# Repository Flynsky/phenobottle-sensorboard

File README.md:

# Phenobottle Sensorboard

## Getting Startet
- Connect via USB or USART0 to access a internal console.
  A good, easy to use Tool for this is the Arduino IDE. 
- Send "?" to this console for help on the avaliable commands.

## Picture

## Hardware

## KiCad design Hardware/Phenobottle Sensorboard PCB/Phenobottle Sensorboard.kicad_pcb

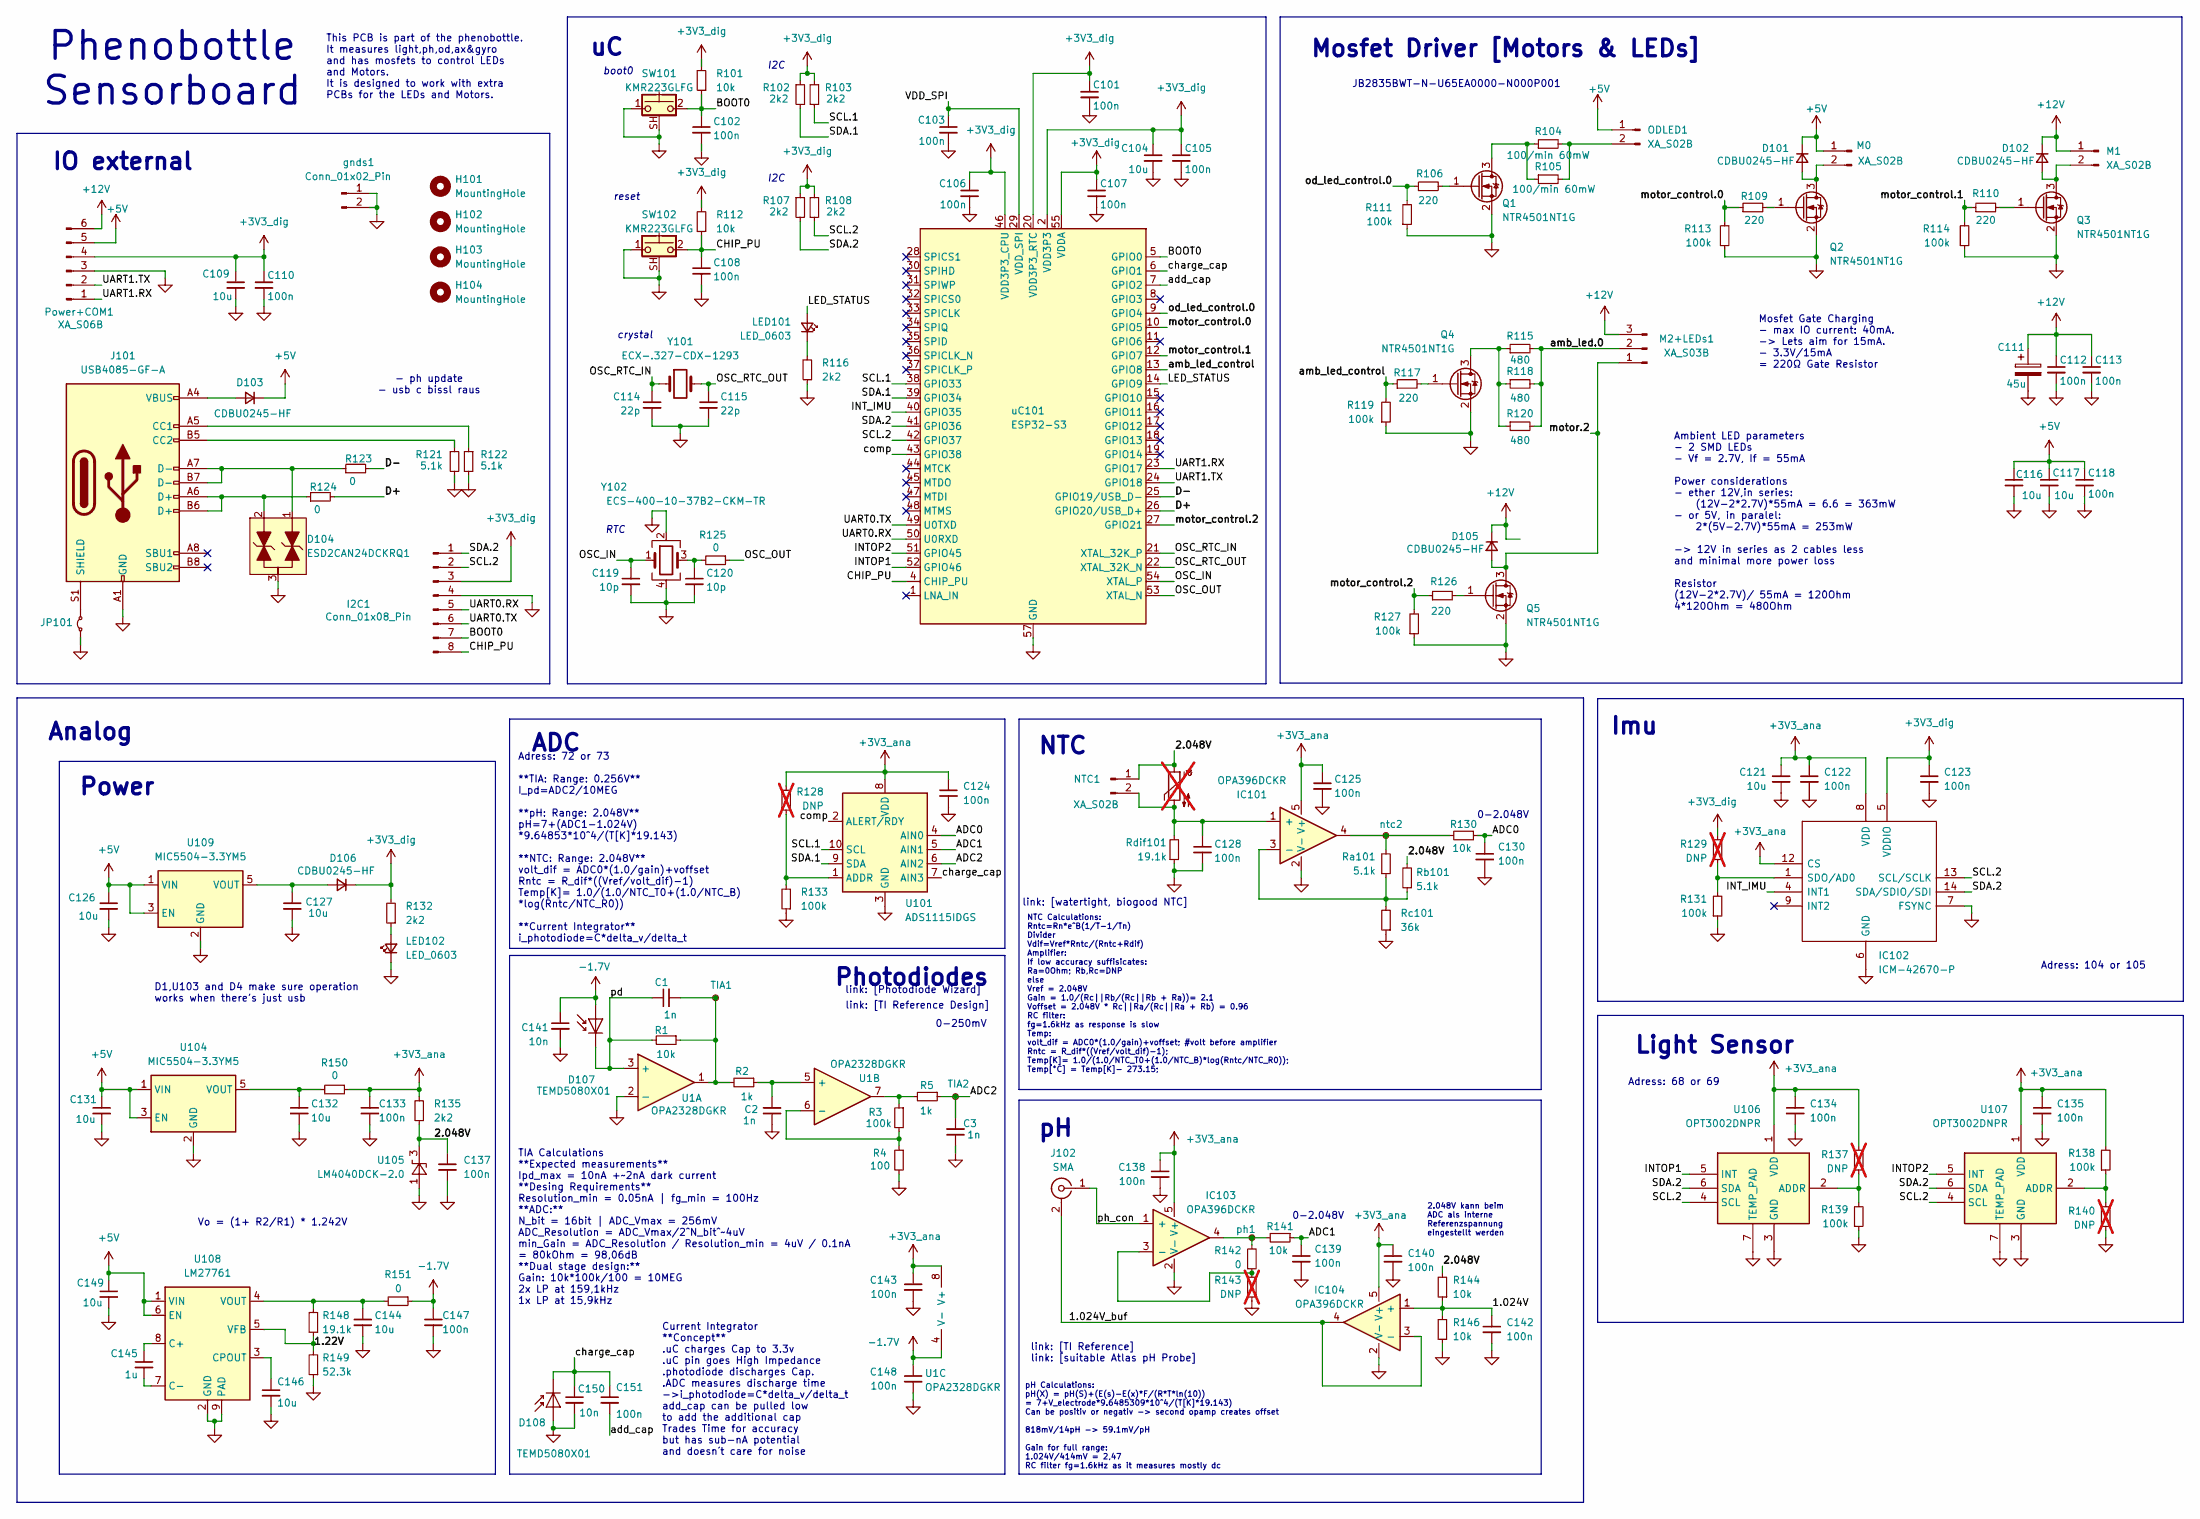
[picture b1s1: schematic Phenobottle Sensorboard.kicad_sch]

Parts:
C1, C2, C3: 1n; C_0603_1608Metric_Pad1.08x0.95mm_HandSolder
C101, C102, C103, C105, C106, C107, C108, C110, C118, C122, C123, C124, C125, C128, C130, C133, C134, C135, C137, C138, C139, C140, C142, C143, C147, C148: 100n; C_0402_1005Metric_Pad0.74x0.62mm_HandSolder
C104, C109, C116, C117, C121, C126, C127, C131, C132, C144, C146, C149: 10u; C_0805_2012Metric_Pad1.18x1.45mm_HandSolder
C111: 45u; CP_Elec_6.3x7.7
C112, C113, C151: 100n; C_0603_1608Metric
C114, C115: 22p; C_0603_1608Metric
C119, C120: 10p; C_0603_1608Metric
C141, C150: 10n; C_0603_1608Metric
C145: 1u; C_0805_2012Metric_Pad1.18x1.45mm_HandSolder
D101, D102, D103, D105, D106: CDBU0245-HF; DIOM179X85N; Mouser Part Number 78-V1FM15-M3/I; mouser 78-V1FM15-M3/I
D104: ESD2CAN24DCKRQ1; SOT-323_SC-70; Manufacturer_Part_Number ESD2CAN24DCKRQ1; Mouser Part Number 595-ESD2CAN24DCKRQ1
D107, D108: TEMD5080X01; Mouser Part Number 720-SFH2440
H101, H102, H103, H104: MountingHole; MountingHole_3.2mm_M3_Pad_Via
I2C1: Conn_01x08_Pin; PinHeader_1x08_P2.54mm_Vertical
IC101, IC103, IC104: OPA396DCKR; SOT65P210X110-5N; Mouser Part Number 595-OPA396DCKR
IC102: ICM-42670-P; ICM42670P; Mouser Part Number 410-ICM-42670-P
J101: USB4085-GF-A; USB_C_Receptacle_GCT_USB4085; Mouser Part Number 640-USB4085-GF-A
J102: SMA; SMA_Wurth_60312002114503_Vertical; Mouser Part Number 737-RF203ET0050G; mouser 471-SMARACONNECTOR
JP101: 0; R_0603_1608Metric_Pad0.98x0.95mm_HandSolder
LED101, LED102: LED_0603; LED_0603_1608Metric_Pad1.05x0.95mm_HandSolder
M0, M1: XA_S02B; JST_XA_S02B-XASK-1_1x02_P2.50mm_Horizontal
M2+LEDs1: XA_S03B; JST_XA_S03B-XASK-1_1x03_P2.50mm_Horizontal
NTC1: XA_S02B; JST_XA_S02B-XASK-1_1x02_P2.50mm_Horizontal
ODLED1: XA_S02B; JST_XA_S02B-XASK-1_1x02_P2.50mm_Horizontal
Power+COM1: XA_S06B; JST_XA_S06B-XASK-1_1x06_P2.50mm_Horizontal
Q1, Q2, Q3, Q4, Q5: NTR4501NT1G; SOT-23-3; Mouser Part Number 863-NTR4501NT1G
R1, R101, R112, R130, R141, R144, R146: 10k; R_0603_1608Metric_Pad0.98x0.95mm_HandSolder
R2, R5: 1k; R_0603_1608Metric_Pad0.98x0.95mm_HandSolder
R3, R111, R113, R114, R119, R127, R131, R133, R138, R139: 100k; R_0603_1608Metric_Pad0.98x0.95mm_HandSolder
R4: 100; R_0603_1608Metric_Pad0.98x0.95mm_HandSolder
R102, R103, R107, R108, R116, R132, R135: 2k2; R_0603_1608Metric_Pad0.98x0.95mm_HandSolder
R104, R105: 100/min 60mW; R_0603_1608Metric_Pad0.98x0.95mm_HandSolder
R106, R109, R110, R117, R126: 220; R_0603_1608Metric_Pad0.98x0.95mm_HandSolder
R115, R118, R120: 480; R_0603_1608Metric_Pad0.98x0.95mm_HandSolder
R121, R122: 5.1k; R_0603_1608Metric_Pad0.98x0.95mm_HandSolder
R123, R124, R125, R142, R150, R151: 0; R_0603_1608Metric_Pad0.98x0.95mm_HandSolder
R128, R129, R137, R140, R143: DNP; R_0603_1608Metric_Pad0.98x0.95mm_HandSolder; not fitted
R148: 19.1k; R_0603_1608Metric_Pad0.98x0.95mm_HandSolder
R149: 52.3k; R_0603_1608Metric_Pad0.98x0.95mm_HandSolder
Ra101: 5.1k; R_0603_1608Metric_Pad0.98x0.95mm_HandSolder
Rb101: 5.1k; R_0603_1608Metric_Pad0.98x0.95mm_HandSolder
Rc101: 36k; R_0603_1608Metric_Pad0.98x0.95mm_HandSolder
Rdif101: 19.1k; R_0603_1608Metric_Pad0.98x0.95mm_HandSolder
SW101, SW102: KMR223GLFG; SW_SPST_CK_KMS2xxGP; Mouser Part Number 611-KMR223GLFG
TH101: Thermistor_NTC; mouser 527-JI-103C1R2-L301; not fitted
TIA1, TIA2: TestPoint_Small; TestPoint_Loop_D2.50mm_Drill1.0mm
U1: OPA2328DGKR; VSSOP-8_SOP65P490X110-8N; Mouser Part Number 595-OPT3002DNPR; mouser 595-OPA2328DGKR
U101: ADS1115IDGS; TSSOP-10_3x3mm_P0.5mm; Mouser Part Number 595-ADS1115IDGSR
U104, U109: MIC5504-3.3YM5; SOT-23-5
U105: LM4040DCK-2.0; SOT-353_SC-70-5; Mouser Part Number 595-M4040EIM7-2.0NPB
U106, U107: OPT3002DNPR; Mouser Part Number 595-OPT3002DNPR
U108: LM27761; WSON-8-1EP_2x2mm_P0.5mm_EP0.9x1.6mm; Mouser Part Number 595-LM27761DSGR
Y101: ECX-.327-CDX-1293; Crystal_SMD_3215-2Pin_3.2x1.5mm; Mouser Part Number 520-ECX-.327CDX-1293
Y102: ECS-400-10-37B2-CKM-TR; Crystal_SMD_2016-4Pin_2.0x1.6mm; Mouser Part Number 520-400-10-37B2CKMTR
gnds1: Conn_01x02_Pin; PinHeader_1x02_P2.54mm_Vertical
ntc2: TestPoint_Small; TestPoint_Loop_D2.50mm_Drill1.0mm
ph1: TestPoint_Small; TestPoint_Loop_D2.50mm_Drill1.0mm
uC101: ESP32-S3; QFN-56-1EP_7x7mm_P0.4mm_EP4x4mm; Mouser Part Number 356-ESP32-S3FH4R2

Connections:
+3V3_ana: C121.1, C122.1, C124.1, C125.1, C133.1, C134.1, C135.1, C138.1, C140.1, C143.1, IC101.5 (V+), IC102.8 (VDD), IC102.12 (CS), IC103.5 (V+), IC104.5 (V+), R128.2, R135.2, R137.1, R138.2, R150.1, U1.8 (V+), U101.8 (VDD), U106.1 (VDD), U107.1 (VDD)
+3V3_dig: C101.1, C104.1, C105.1, C106.1, C107.1, C109.1, C110.1, C123.1, D106.1 (K), I2C1.3, IC102.5 (VDDIO), Power+COM1.4, R101.2, R102.1, R103.1, R107.1, R108.1, R112.2, R129.1, R132.2, uC101.2 (VDD3P3), uC101.3 (VDD3P3), uC101.20 (VDD3P3_RTC), uC101.46 (VDD3P3_CPU), uC101.55 (VDDA), uC101.56 (VDDA)
+5V: C116.1, C117.1, C118.1, C126.1, C131.1, C149.1, D101.1 (K), D103.1 (K), M0.1, ODLED1.1, Power+COM1.5, U104.1 (VIN), U104.3 (EN), U108.1 (VIN), U108.6 (EN), U109.1 (VIN), U109.3 (EN)
+12V: C111.1, C112.1, C113.1, D102.1 (K), D105.1 (K), M1.1, M2+LEDs1.3, Power+COM1.6
-1.7V: C141.1, C147.1, C148.1, D107.2 (A), R151.1, U1.4 (V-)
/1.22V: R148.1, R149.2, U108.5 (VFB)
/1.024V: C142.1, IC104.1 (+), R144.1, R146.2
/1.024V_buf: IC104.3 (-), IC104.4, J102.2 (Ext)
/2.048V: C137.1, NTC1.1, R135.1, R144.2, Rb101.2, TH101.1, U105.3 (K)
/ADC0: C130.1, R130.1, U101.4 (AIN0)
/ADC1: C139.1, R141.1, U101.5 (AIN1)
/ADC2: C3.2, R5.1, TIA2.1, U101.6 (AIN2)
/BOOT0: C102.1, I2C1.7, R101.1, SW101.2, uC101.5 (GPIO0)
/CHIP_PU: C108.1, I2C1.8, R112.1, SW102.2, uC101.4 (CHIP_PU)
/D+: R124.2, uC101.26 (GPIO20/USB_D+)
/D-: R123.2, uC101.25 (GPIO19/USB_D-)
/INTOP1: U106.5 (INT), uC101.52 (GPIO46)
/INTOP2: U107.5 (INT), uC101.51 (GPIO45)
/INT_IMU: IC102.4 (INT1), uC101.40 (GPIO35)
/LED_STATUS: LED101.2 (A), uC101.14 (GPIO9)
/OSC_IN: C119.1, Y102.1, uC101.54 (XTAL_P)
/OSC_OUT: R125.1, uC101.53 (XTAL_N)
/OSC_RTC_IN: C114.1, Y101.1, uC101.21 (XTAL_32K_P)
/OSC_RTC_OUT: C115.1, Y101.2, uC101.22 (XTAL_32K_N)
/SCL.1: R103.2, U101.10 (SCL), uC101.38 (GPIO33)
/SCL.2: I2C1.2, IC102.13 (SCL/SCLK), R108.2, U106.4 (SCL), U107.4 (SCL), uC101.42 (GPIO37)
/SDA.1: R102.2, U101.9 (SDA), uC101.39 (GPIO34)
/SDA.2: I2C1.1, IC102.14 (SDA/SDIO/SDI), R107.2, U106.6 (SDA), U107.6 (SDA), uC101.41 (GPIO36)
/UART0.RX: I2C1.5, uC101.50 (U0RXD)
/UART0.TX: I2C1.6, uC101.49 (U0TXD)
/UART1.RX: Power+COM1.1, uC101.23 (GPIO17)
/UART1.TX: Power+COM1.2, uC101.24 (GPIO18)
/VDD_SPI: C103.1, uC101.29 (VDD_SPI)
/add_cap: C151.2, uC101.7 (GPIO2)
/amb_led.0: M2+LEDs1.2, R115.2, R118.2, R120.2
/amb_led_control: R117.1, R119.2, uC101.13 (GPIO8)
/charge_cap: C150.1, C151.1, D108.1 (K), U101.7 (AIN3), uC101.6 (GPIO1)
/comp: U101.2 (ALERT/RDY), uC101.43 (GPIO38)
/motor.2: D105.2 (A), M2+LEDs1.1, Q5.3 (D)
/motor_control.0: R109.1, R113.2, uC101.10 (GPIO5)
/motor_control.1: R110.1, R114.2, uC101.12 (GPIO7)
/motor_control.2: R126.1, R127.2, uC101.27 (GPIO21)
/od_led_control.0: R106.1, R111.2, uC101.9 (GPIO4)
/pd: C1.1, D107.1 (K), R1.2, U1.3 (+)
/ph_con: IC103.1 (+), J102.1 (In)
GND: C2.1, C3.1, C101.2, C102.2, C103.2, C104.2, C105.2, C106.2, C107.2, C108.2, C109.2, C110.2, C111.2, C112.2, C113.2, C114.2, C115.2, C116.2, C117.2, C118.2, C119.2, C120.2, C121.2, C122.2, C123.2, C124.2, C125.2, C126.2, C127.2, C128.2, C130.2, C131.2, C132.2, C133.2, C134.2, C135.2, C137.2, C138.2, C139.2, C140.2, C141.2, C142.2, C143.2, C144.2, C146.2, C147.2, C148.2, C149.2, C150.2, D104.3, D108.2 (A), I2C1.4, IC101.2 (V-), IC102.6 (GND), IC102.7 (FSYNC), IC103.2 (V-), IC104.2 (V-), J101.A1 (GND), J101.A12 (GND), J101.B1 (GND), J101.B12 (GND), JP101.1 (A), LED102.1 (K), Power+COM1.3, Q1.2 (S), Q2.2 (S), Q3.2 (S), Q4.2 (S), Q5.2 (S), R4.2, R111.1, R113.1, R114.1, R116.1, R119.1, R121.2, R122.2, R127.1, R131.1, R133.1, R139.1, R140.2, R143.1, R146.1, R149.1, Rc101.1, Rdif101.1, SW101.1, SW101.SH (B), SW102.1, SW102.SH (B), U1.2 (-), U101.3 (GND), U104.2 (GND), U105.1 (A), U106.3 (GND), U106.7 (TEMP_PAD), U107.3 (GND), U107.7 (TEMP_PAD), U108.2 (GND), U108.9 (PAD), U109.2 (GND), Y102.2, Y102.4, gnds1.1, gnds1.2, uC101.57 (GND)
unnamed: C1.2, R1.1, R2.2, TIA1.1, U1.1
unnamed: C120.1, R125.2, Y102.3
unnamed: D101.2 (A), M0.2, Q2.3 (D)
unnamed: D102.2 (A), M1.2, Q3.3 (D)
unnamed: D103.2 (A), J101.A4 (VBUS), J101.A9 (VBUS), J101.B4 (VBUS), J101.B9 (VBUS)
unnamed: D104.1, J101.A7 (D-), J101.B7 (D-), R123.1
unnamed: D104.2, J101.A6 (D+), J101.B6 (D+), R124.1
unnamed: C127.1, D106.2 (A), U109.5 (VOUT)
unnamed: C128.1, IC101.1 (+), NTC1.2, Rdif101.2, TH101.2
unnamed: IC101.3 (-), Ra101.1, Rb101.1, Rc101.2
unnamed: IC101.4, R130.2, Ra101.2, ntc2.1
unnamed: IC102.1 (SDO/AD0), R129.2, R131.2
unnamed: IC103.3 (-), R142.1, R143.2
unnamed: IC103.4, R141.2, R142.2, ph1.1
unnamed: J101.A5 (CC1), R122.1
unnamed: J101.B5 (CC2), R121.1
unnamed: J101.S1 (SHIELD), JP101.2 (B)
unnamed: LED101.1 (K), R116.2
unnamed: LED102.2 (A), R132.1
unnamed: ODLED1.2, R104.2, R105.2
unnamed: Q1.3 (D), R104.1, R105.1
unnamed: Q1.1 (G), R106.2
unnamed: Q2.1 (G), R109.2
unnamed: Q3.1 (G), R110.2
unnamed: Q4.3 (D), R115.1, R118.1, R120.1
unnamed: Q4.1 (G), R117.2
unnamed: Q5.1 (G), R126.2
unnamed: R3.1, R5.2, U1.7
unnamed: C2.2, R2.1, U1.5 (+)
unnamed: R3.2, R4.1, U1.6 (-)
unnamed: R128.1, R133.2, U101.1 (ADDR)
unnamed: C132.1, R150.2, U104.5 (VOUT)
unnamed: R137.2, R139.2, U106.2 (ADDR)
unnamed: R138.1, R140.1, U107.2 (ADDR)
unnamed: C145.1, U108.8 (C+)
unnamed: C145.2, U108.7 (C-)
unnamed: C146.1, U108.3 (CPOUT)
unnamed: C144.1, R148.2, R151.2, U108.4 (VOUT)

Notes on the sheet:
Analog
Phenobottle Sensorboard
link: [TI Reference]
reset
boot0
I2C
link: [suitable Atlas pH Probe]
link: [watertight, biogood NTC]
ADC
crystal
Mosfet Driver [Motors & LEDs]
- ph update - usb c bissl raus
Light Sensor
IO external
link: [TI Reference Design]
0-250mV
0-2.048V
Photodiodes
link: [Photodiode Wizard]
Imu
Power
D1,U103 and D4 make sure operation works when there's just usb
NTC
JB2835BWT-N-U65EA0000-N000P001
RTC
Adress: 72 or 73 **TIA: Range: 0.256V** I_pd=ADC2/10MEG **pH: Range: 2.048V** pH=7+(ADC1-1.024V) *9.64853*10^4/(T[K]*19.143) **NTC: Range: 2.048V** volt_dif = ADC0*(1.0/gain)+voffset Rntc = R_dif*((Vref/volt_dif)-1) Temp[K]= 1.0/(1.0/NTC_T0+(1.0/NTC_B) *log(Rntc/NTC_R0)) **Current Integrator** i_ph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
2.048V kann beim ADC als interne Referenzspannung eingestellt werden
Current Integrator **Concept** .uC charges Cap to 3.3v .uC pin goes High Impedance .photodiode discharges Cap. .ADC measures discharge time ->i_photodiode=C*delta_v/delta_t add_cap can be pulled low to add the additional cap Trades Time for accuracy but has sub-nA potential and doesn´t care for noi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
Mosfet Gate Charging - max IO current: 40mA. -> Lets aim for 15mA. - 3.3V/15mA = 220Ω Gate Resistor
This PCB is part of the phenobottle. It measures light,ph,od,ax&gyro and has mosfets to control LEDs and Motors. It is designed to work with extra PCBs for the LEDs and Motors.
Adress: 104 or 105
pH Calculations: pH(X) = pH(S)+(E(s)-E(x)*F/(R*T*ln(10)) = 7+V_electrode*9.6485309*10^4/(T[K]*19.143) Can be positiv or negativ -> second opamp creates offset 818mV/14pH -> 59.1mV/pH Gain for full range: 1.024V/414mV = 2,47 RC filter fg=1.6kHz as it measures mostly dc
NTC Calculations: Rntc=Rn*e^B(1/T-1/Tn) Divider Vdif=Vref*Rntc/(Rntc+Rdif) Amplifier: If low accuracy suffisicates: Ra=0Ohm; Rb,Rc=DNP else Vref = 2.048V Gain = 1.0/(Rc||Rb/(Rc||Rb + Ra))= 2.1 Voffset = 2.048V * Rc||Ra/(Rc||Ra + Rb) = 0.96 RC filter: fg=1.6kHz as response is slow Temp: volt_dif = A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
Adress: 68 or 69
Ambient LED parameters - 2 SMD LEDs - Vf = 2.7V, If = 55mA Power considerations - ether 12V,in series: (12V-2*2.7V)*55mA = 6.6 = 363mW - or 5V, in paralel: 2*(5V-2.7V)*55mA = 253mW -> 12V in series as 2 cables less and minimal more power loss Resistor (12V-2*2.7V)/ 55mA = 120Ohm 4*120Ohm = 480Ohm
Vo = (1+ R2/R1) * 1.242V
TIA Calculations **Expected measurements** Ipd_max = 10nA +~2nA dark current **Desing Requirements** Resolution_min = 0.05nA | fg_min = 100Hz **ADC:** N_bit = 16bit | ADC_Vmax = 256mV ADC_Resolution = ADC_Vmax/2^N_bit^~4uV min_Gain = ADC_Resolution / Resolution_min = 4uV / 0.1nA = 80kOhm = 98,06dB 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

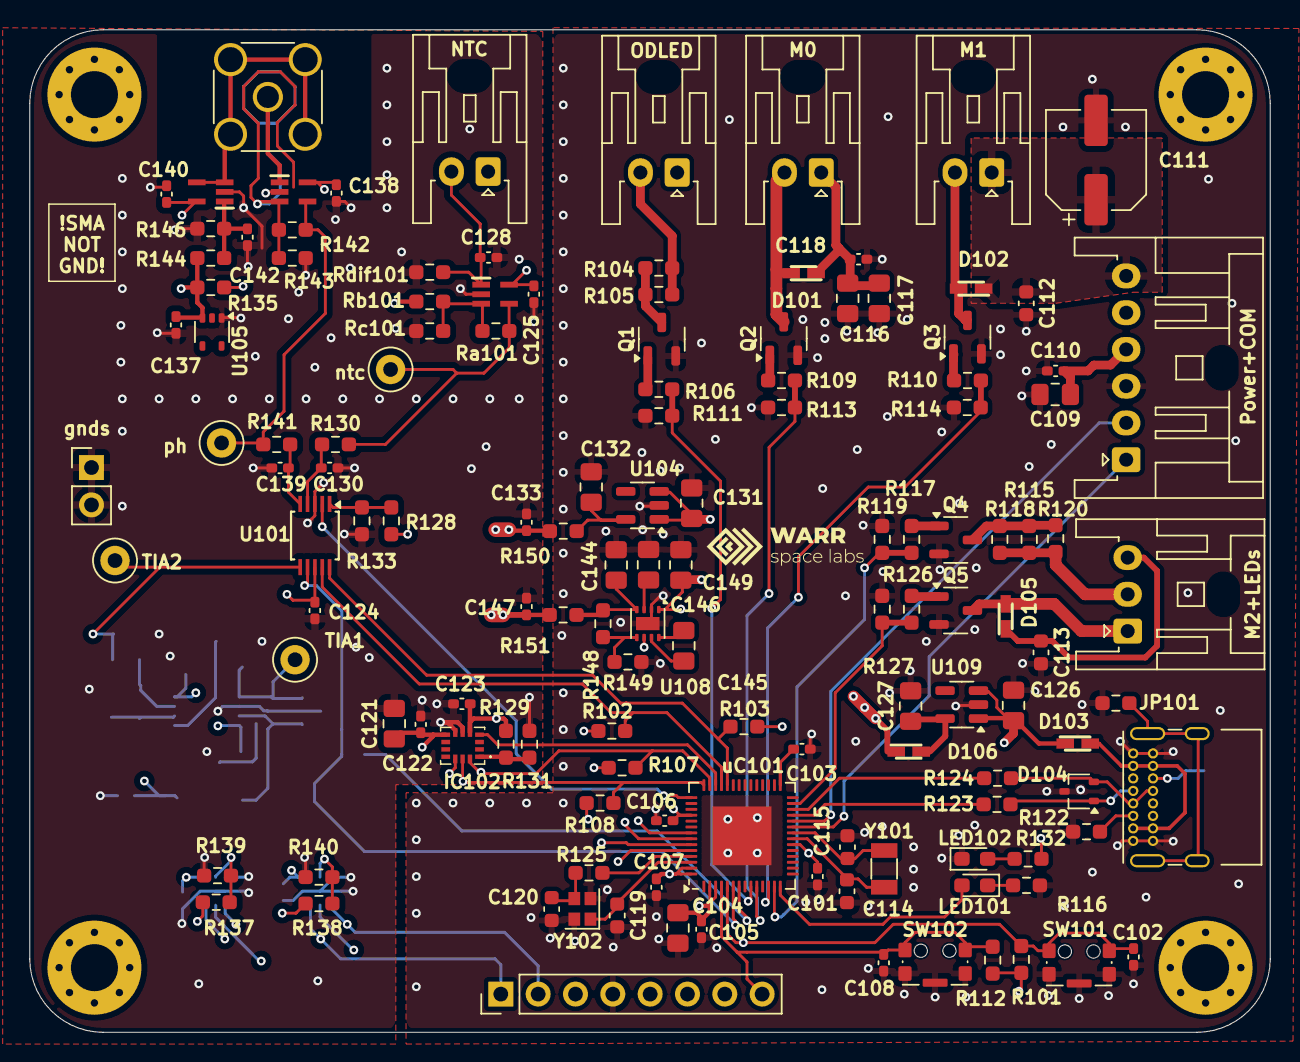
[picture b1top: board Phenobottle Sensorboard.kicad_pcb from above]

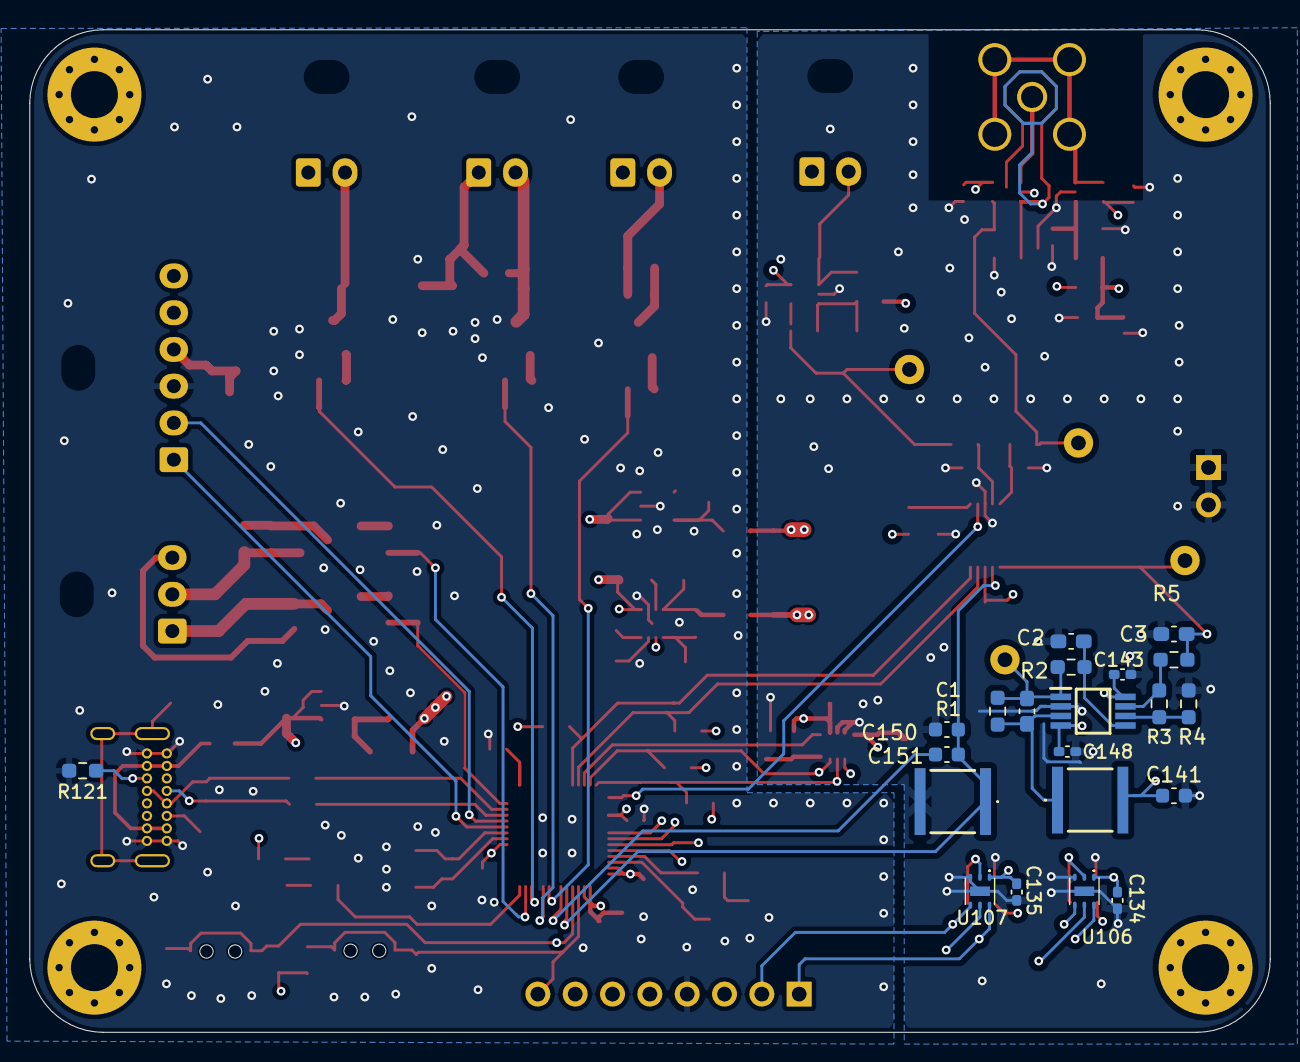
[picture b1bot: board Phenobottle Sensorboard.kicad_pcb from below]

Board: 4 copper layers, 84.4 x 68.2 mm, 159 parts (21 on the bottom side), 84 nets.

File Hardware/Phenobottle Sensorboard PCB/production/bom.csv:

Designator,Footprint,Quantity,Value,LCSC Part #
"C1, C2, C3",0603,3,1n,
"C101, C102, C103, C105, C106, C107, C108, C110, C118, C122, C123, C124, C125, C128, C130, C133, C134, C135, C137, C138, C139, C140, C142, C143, C147, C148",0402,26,100n,
"C104, C109, C116, C117, C121, C126, C127, C131, C132, C144, C146, C149",0805,12,10u,
C111,CP_Elec_6.3x7.7,1,45u,
"C112, C113, C151",0603,3,100n,
"C114, C115",0603,2,22p,
"C119, C120",0603,2,12p,
"C141, C150",0603,2,10n,
C145,0805,1,1u,
"D101, D102, D103, D105, D106",DIOM179X85N,5,CDBU0245-HF,
D104,SOT-323_SC-70,1,ESD2CAN24DCKRQ1,
"D107, D108",TEMD5080X01,2,TEMD5080X01,
GNDS1,PinHeader_1x02_P2.54mm_Vertical,1,Conn_01x02_Pin,
I2C1,PinHeader_1x08_P2.54mm_Vertical,1,Conn_01x08_Pin,
"IC101, IC103, IC104",SOT65P210X110-5N,3,OPA396DCKR,
IC102,ICM42670P,1,ICM-42670-P,
J101,USB_C_Receptacle_GCT_USB4085,1,USB4085-GF-A,
J102,SMA_Wurth_60312002114503_Vertical,1,SMA,
"JP101, R123, R124, R125, R142, R150, R151",0603,7,0,
"LED101, LED102",0603,2,LED_0603,
"M0, M1, NTC1, ODLED1",JST_XA_S02B-XASK-1_1x02_P2.50mm_Horizontal,4,XA_S02B,
M2+LEDS1,JST_XA_S03B-XASK-1_1x03_P2.50mm_Horizontal,1,XA_S03B,
POWER+COM1,JST_XA_S06B-XASK-1_1x06_P2.50mm_Horizontal,1,XA_S06B,
"Q1, Q2, Q3, Q4, Q5",SOT-23-3,5,NTR4501NT1G,
"R1, R101, R112, R130, R141, R144, R146",0603,7,10k,
"R102, R103, R107, R108, R116, R132, R135",0603,7,2k2,
"R104, R105",0603,2,100/min 60mW,
"R106, R109, R110, R117, R126",0603,5,220,
"R111, R113, R114, R119, R127, R131, R133, R138, R139, R3",0603,10,100k,
"R115, R118, R120",0603,3,480,
"R121, R122, RA101, RB101",0603,4,5.1k,
"R148, RDIF101",0603,2,20k,
R149,0603,1,50k,
"R2, R5",0603,2,1k,
R4,0603,1,100,
RC101,0603,1,40k,
"SW101, SW102",SW_SPST_CK_KMS2xxGP,2,KMR223GLFG,
"TIA1, TIA2",TestPoint_Loop_D2.50mm_Drill1.0mm,2,TestPoint_Small,
U1,VSSOP-8_SOP65P490X110-8N,1,OPA2328DGKR,
U101,TSSOP-10_3x3mm_P0.5mm,1,ADS1115IDGS,
"U104, U109",SOT-23-5,2,MIC5504-3.3YM5,
U105,SOT-353_SC-70-5,1,LM4040DCK-2.0,
"U106, U107",OPT3002DNPR,2,OPT3002DNPR,
U108,WSON-8-1EP_2x2mm_P0.5mm_EP0.9x1.6mm,1,LM27761,
UC101,QFN-56-1EP_7x7mm_P0.4mm_EP4x4mm,1,ESP32-S3,
Y101,Crystal_SMD_3215-2Pin_3.2x1.5mm,1,ECX-.327-CDX-1293,
Y102,Crystal_SMD_2016-4Pin_2.0x1.6mm,1,ECS-400-10-37B2-CKM-TR,

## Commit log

2025-11-25 moved
2025-11-25 Readme updated
2025-11-25 Fix image links in README for proper display
    Updated image links in README to use URL encoding.
2025-11-25 Update README to simplify hardware documentation
    Removed software setup section and redundant schematic image.
